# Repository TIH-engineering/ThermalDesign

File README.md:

# ThermalDesign

## 🔌 Leiterplattenbeschreibung

Die Leiterplatte **ThermalDesign** dient zur praktischen Untersuchung des **thermischen Verhaltens elektronischer Bauteile**. Als Versuchsobjekt werden mehrere LM317-Linearregler unter unterschiedlichen thermischen Bedingungen und bei verschiedenen Belastungen betrieben.

Die Leiterplatte enthält vier vergleichbare Spannungsreglerstufen mit einer Ausgangsspannung von etwa **2,5 V**. Die Regler unterscheiden sich insbesondere hinsichtlich ihrer thermischen Anbindung:

- **LM317 im SOT-223-Gehäuse**
- **LM317 im TO-220-Gehäuse**
- **LM317 im SOT-223-Gehäuse mit zusätzlicher Kupferfläche zur Wärmeabfuhr**
- **LM317 im TO-220-Gehäuse mit Kühlkörper**

Über verschiedene Lastwiderstände können unterschiedliche Lastfälle eingestellt werden. Vorgesehen sind Untersuchungen bei ungefähr:

- **100 mA**
- **250 mA**
- **500 mA**
- **1 A** als gepulste Last

Die 1-A-Last wird über einen MOSFET geschaltet und kann mit einem externen PWM-Signal angesteuert werden. Dadurch lassen sich neben stationären Temperaturzuständen auch **dynamische Erwärmungs- und Abkühlvorgänge** untersuchen.

Mit der Leiterplatte können unter anderem der Zusammenhang zwischen **Verlustleistung, Bauteiltemperatur, thermischem Widerstand, Gehäusebauform, Kupferfläche und Kühlkörper** experimentell untersucht werden. Die Messergebnisse können mit theoretischen Berechnungen oder thermischen Ersatzschaltbildern verglichen werden.

> **Einsatzgebiet:** Laborübungen und Unterricht zu thermischem Design, Verlustleistung, Wärmewiderständen, Linearreglern und Kühlung elektronischer Bauteile

---

## 📥 Downloads

| Datei | Beschreibung |
|---|---|
| 📄 [Schaltplan (PDF)](../../releases/latest/download/schematic.pdf) | Schaltplan der Leiterplatte |
| 🖨️ [Leiterplatte (PDF)](../../releases/latest/download/pcb.pdf) | Leiterplattenansicht als PDF |
| 🔩 [Bohrplan (PDF)](../../releases/latest/download/drill.pdf) | Bohrdaten / Bohrplan |
| 📋 [Stückliste (Excel)](../../releases/latest/download/bom.xlsx) | Bill of Materials |
| 🌐 [Interactive BOM](../../releases/latest/download/ibom.html) | Interaktive Bestückungsansicht |
| 📦 [Fertigungsdaten](../../releases/latest/download/kicad.zip) | Gerber- und Bohrdaten |
| 🧊 [STEP-Modell](../../releases/latest/download/pcb.step) | 3D-Modell der Leiterplatte |

Die Dateien werden automatisch durch den Release-Workflow erzeugt.

---

## 🖥️ Leiterplatte

### Vorschau

| Oberseite | Unterseite |
|:---:|:---:|
|  |  |

### Oberseite

### Unterseite

---

## ℹ️ Projektinformationen

| Eigenschaft | Wert |
|---|---|
| **Projekt** | ThermalDesign |
| **Software** | KiCad 10 |
| **Repository** | TIH-engineering/ThermalDesign |
| **Autor** | [TIH] |
| **Lizenz** | CC BY-NC-SA 4.0 |

---

## 🗂️ Repository-Struktur

```text
.
├── .github/
│   └── workflows/       # GitHub Actions
├── .kibot/              # KiBot-Konfiguration
├── pcb/
│   ├── lib/             # Projektspezifische Bibliotheken
│   └── ...              # KiCad-Projektdateien
├── .gitignore
├── LICENSE
└── README.md

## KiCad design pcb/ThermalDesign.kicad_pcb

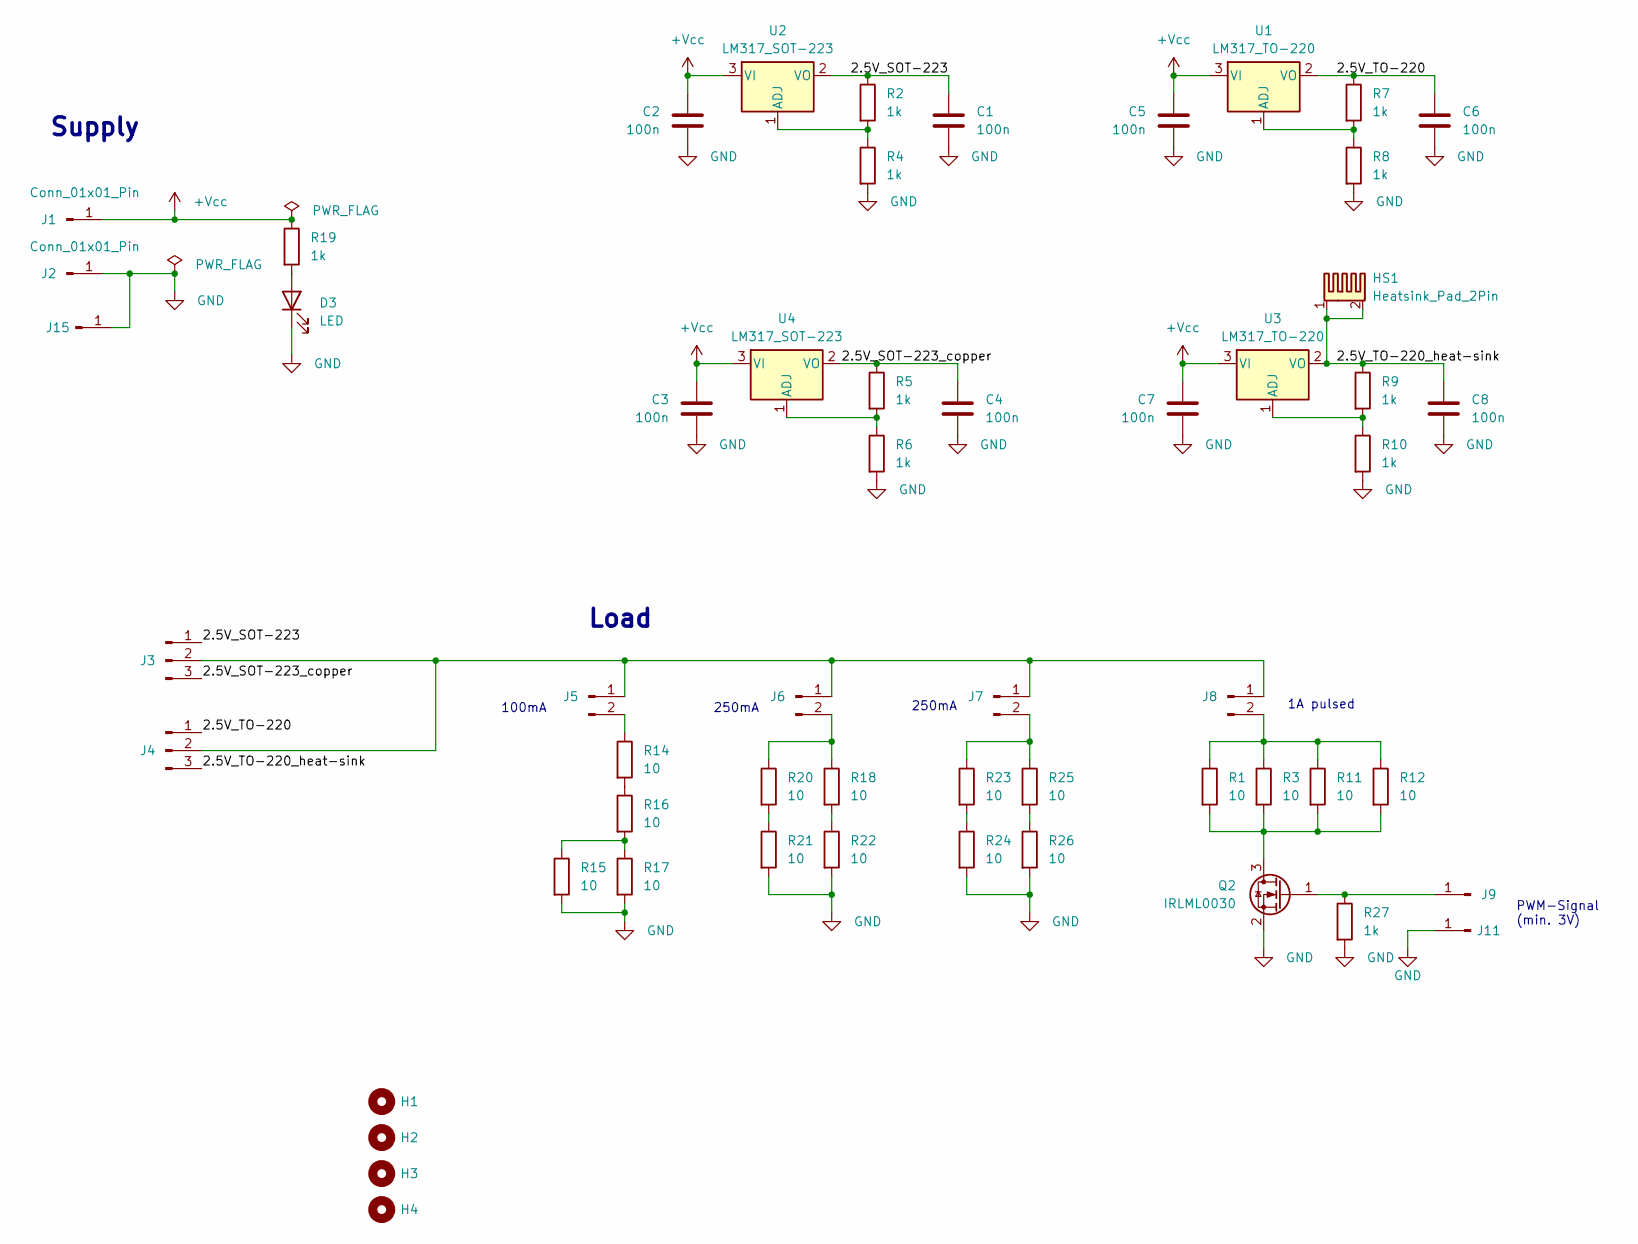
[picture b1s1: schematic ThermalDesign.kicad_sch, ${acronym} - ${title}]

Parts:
C1, C2, C3, C4, C5, C6, C7, C8: 100n; C_1206_3216Metric
D3: LED; LED_1206_3216Metric
H1, H2, H3, H4: MountingHole; MountingHole_3.2mm_M3
HS1: Heatsink_Pad_2Pin; Heatsink_Fischer_SK129-STS_42x25mm_2xDrill2.5mm
J1, J2, J9, J11, J15: Conn_01x01_Pin; PinHeader_1x01_P2.54mm_Vertical
J3, J4: Conn_01x03_Pin; PinHeader_1x03_P2.54mm_Vertical
J5, J6, J7, J8: Conn_01x02_Pin; PinHeader_1x02_P2.54mm_Vertical
Q2: IRLML0030; SOT-23
R1, R3, R11, R12, R14, R15, R16, R17, R18, R20, R21, R22, R23, R24, R25, R26: 10; R_1206_3216Metric
R2, R4, R5, R6, R7, R8, R9, R10, R19, R27: 1k; R_1206_3216Metric
U1, U3: LM317_TO-220; TO-220-3_Vertical
U2, U4: LM317_SOT-223; SOT-223-3_TabPin2

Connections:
+Vcc: C2.1, C3.1, C5.1, C7.1, J1.1 (Pin_1_1), R19.1, U1.3 (VI), U2.3 (VI), U3.3 (VI), U4.3 (VI)
/2.5V_SOT-223: C1.1, J3.1, R2.1, U2.2 (VO)
/2.5V_SOT-223_copper: C4.1, J3.3, R5.1, U4.2 (VO)
/2.5V_TO-220: C6.1, J4.1, R7.1, U1.2 (VO)
/2.5V_TO-220_heat-sink: C8.1, HS1.1, HS1.2, J4.3, R9.1, U3.2 (VO)
GND: C1.2, C2.2, C3.2, C4.2, C5.2, C6.2, C7.2, C8.2, D3.1 (K), J2.1 (Pin_1_1), J11.1 (Pin_1_1), J15.1 (Pin_1_1), Q2.2 (S), R4.2, R6.2, R8.2, R10.2, R15.2, R17.2, R21.2, R22.2, R24.2, R26.2, R27.2
unnamed: D3.2 (A), R19.2
unnamed: J3.2, J4.2, J5.1, J6.1, J7.1, J8.1
unnamed: J5.2, R14.1
unnamed: J6.2, R18.1, R20.1
unnamed: J7.2, R23.1, R25.1
unnamed: J8.2, R1.1, R3.1, R11.1, R12.1
unnamed: J9.1 (Pin_1_1), Q2.1 (G), R27.1
unnamed: Q2.3 (D), R1.2, R3.2, R11.2, R12.2
unnamed: R14.2, R16.1
unnamed: R15.1, R16.2, R17.1
unnamed: R18.2, R22.1
unnamed: R20.2, R21.1
unnamed: R23.2, R24.1
unnamed: R25.2, R26.1
unnamed: R7.2, R8.1, U1.1 (ADJ)
unnamed: R2.2, R4.1, U2.1 (ADJ)
unnamed: R9.2, R10.1, U3.1 (ADJ)
unnamed: R5.2, R6.1, U4.1 (ADJ)

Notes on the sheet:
250mA
PWM-Signal (min. 3V)
Supply
100mA
Load
1A pulsed

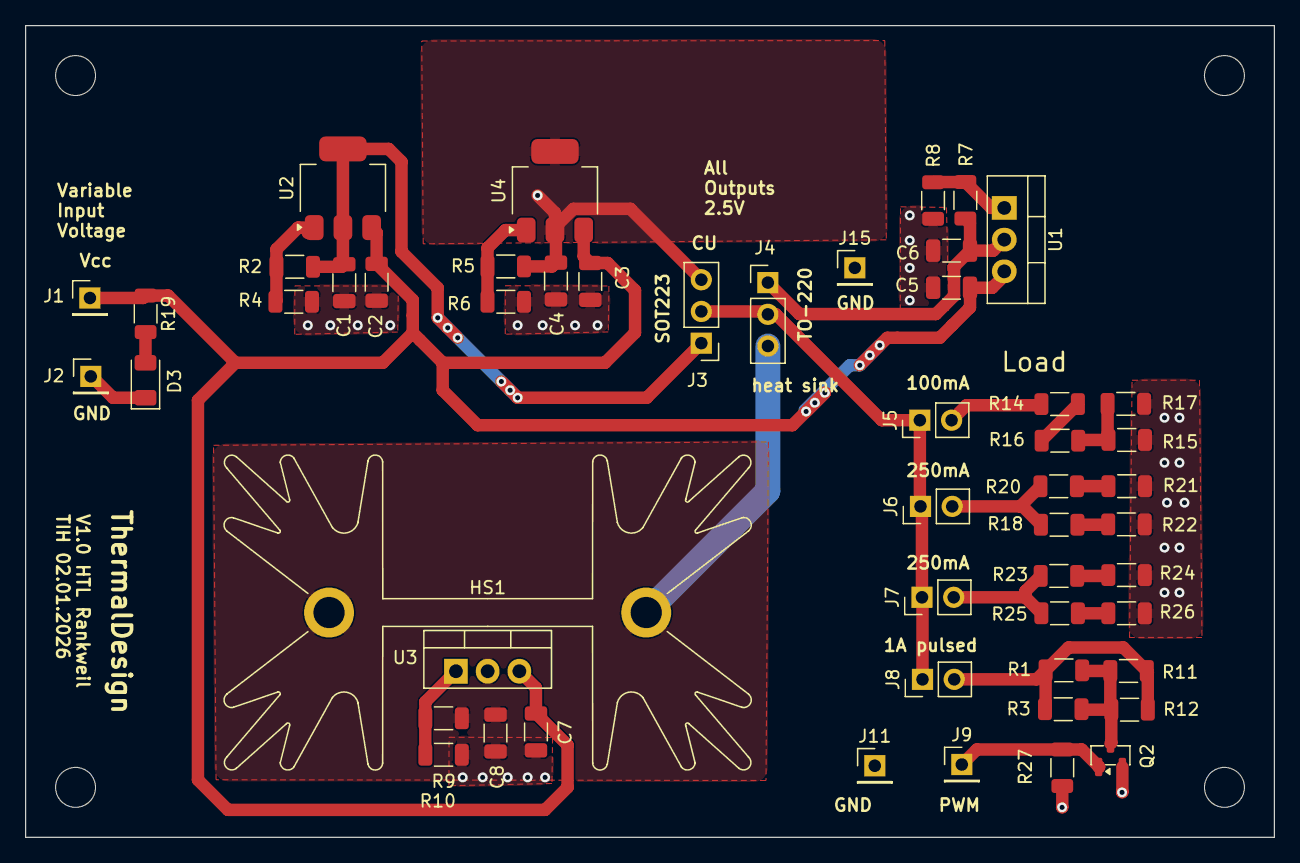
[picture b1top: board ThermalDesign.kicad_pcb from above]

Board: 2 copper layers, 100.0 x 65.0 mm, 56 parts (0 on the bottom side), 24 nets.

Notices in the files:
README.md:
License: CC-BY-NC-SA-4.0
